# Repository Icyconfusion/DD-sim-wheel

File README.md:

# DD-sim-wheel
A Direct Drive (DD) wheel for simracing using a hoverboard motor and CAN bus.

I designed this wheel for simracing, to compete with high end direct drive wheels that offer great quality force feedback, except with a much lower price. The wheel has the capability to connect wheel rims, pedals, shifters, handbrakes etc and send those inputs, along with steering position to the PC as game inputs. In creating this project, I learned a lot about motor control and half bridge drivers.

# Assembly

The project can be separated into two parts, the wheelbase and the wheel rim.

For the wheelbase, the assembly consists of four horizontal 2020 profiles, allowing for mounting to rigs etc, and providing the basic structure of the base. Two vertical posts are attached by 90 degree connectors to enable mounting the cross beam for the motor.

The crossbeam (2040 profile) is important as it is the base structure for supporting and holding the motor in place. A thin steel plate (necessary to prevent damage and subsequent twisting of the the crossbeam as a result of the motor axle) is attached to the profile, with the flat part of the motor axle being locked on with the 3d printed clamp. This is the mechanism for holding the motor in place and preventing rotation in the axle. 

To prepare the motor, it is first necessary to disassemble it. First remove the tire as this wont be needed. Then remove the motor bell as we will need to drill holes into it. We will also need to drill into the axle. a 6x70mm bolt pattern is drilled in to the bell face, as well as a 30mm hole in the centre. This allows the mounting of the encoder and routing of wires. Drill a hole in the closed end of the axle, so that wires can run through.

The MT6701 encoder is attached to its mount, then press fit into the bearing on the bell side of the motor.

The diametric magnet for the encoder is glued into the hole on the inside of the magnet mount, this will be attached to the motor along with the quick release using the 6x70mm drilled holes.

The side covers attach to the four horizontal profiles using T nuts, and the PSU is mounted to the side cover using the mounting threads in the psu. The PCB is attached to its mount using the mounting holes, then attached to the vertical profile.

The USB C connectors are screwed onto the back plate, and power cables run through the two holes. The back, top and bottom plates/covers are mounted using T nuts.

The front plate is screwed directly into the tapped ends of the profiles. This is the wheelbase assembly.

For the wheel rim assembly, is is as simple as mounting the 12mm buttons using the nuts included, running the cable from the mcu into the USB c connector in the quick release, and then mounting the wheel rim, buttons box/plates and quick release using screws, and then pushing onto wheelbase.

# Electronics

### Schematic

I made my own 3 phase motor driver to handle the control of the hoverboard motor:

It uses an INA240 for current sensing for torque control, and an IR2104 IC so that the STM32 can control the MOSFETS.

Screw terminals to external connections:

And brake resistor circuit:

### PCB

It has M6 mounting holes for the wheelbase PCB mount. The PCB is organised with the motor driver at the top, and low voltage components below the STM32, which is connected by headers. It uses TO-220 mosfets, and 7.62mm screw terminals. The screw terminals on the bottom are to CAN connections, encoder and 5v power.

# Firmware

The wheelbase uses a modified version of OpenFFBoard firmware. OpenFFboard controls the motor including torque, responding to output from the PC/game to provide force feedback. I added my own CAN firmware into this to recieve CAN messages as inputs, and send them to the PC. This included writing my own CAN callback into the firmware.
For the wheel rim MCU, I wrote my own firmware for reading button inputs, and then sending via CAN bus. The MCU will only send a message when their is a change in button states e.g a press or release, this is to reduce interruption to the motor control firmware. The can message is as follows: if button one is pressed, then 00000001, which is 1x01. Or if buttons 1 and 4 are pressed, 00001001, 0x09.

# BOM

### Parts
|    Name                  |                                              Purpose                                                          |  Quantity  | Total cost (USD)      |     Link                                                                                                                                                                                                                                                                                                                                                                                                                                                                                                                                                                                                                                                                                                                                                             | Distributor           |
|------------------------|------------------------------------------------------------------------------------------------------------------------------|----|-------|------------------------------------------------------------------------------------------------------------------------------------------------------------------------------------------------------------------------------------------------------------------------------------------------------------------------------------------------------------------------------------------------------------------------------------------------------------------------------------------------------------------------------------------------------------------------------------------------------------------------------------------------------------------------------------------------------------------------------------------------------------------------------------|------------|
| 10 ohm resistor        | Resistor for the PCB                                                                                                         | 5  | 1.32  | https://www.aliexpress.com/item/1005001437016232.html?spm=a2g0o.productlist.main.25.79ca1H2A1H2AOB&algo_pvid=20ba9475-3400-47e4-a338-b3b9dafa6b8d&algo_exp_id=20ba9475-3400-47e4-a338-b3b9dafa6b8d-22&pdp_ext_f=%7B%22order%22%3A%22131%22%2C%22eval%22%3A%221%22%2C%22fromPage%22%3A%22search%22%7D&pdp_npi=6%40dis%21AUD%211.57%211.41%21%21%211.10%210.99%21%402101dedf17721606578806807eb6a1%2112000016109444174%21sea%21AU%210%21ABX%211%210%21n_tag%3A-29910%3Bd%3A6fbdfe4b%3Bm03_new_user%3A-29895%3BpisId%3A5000000197838623&curPageLogUid=U5uodymgkUGQ&utparam-url=scene%3Asearch%7Cquery_from%3A%7Cx_object_id%3A1005001437016232%7C_p_origin_prod%3A                                                                                                                    | Aliexpress |
| 90 degree brackets     | mounting and assembling T slot profiles                                                                                      | 8  | 0.73  | https://jlcmc.com/product/s/T02/TPDB/die-cast-corner-bracket-eu-20-series-connector?k=TPDB-206-2020&productModelNumber=TPDB-206-2020                                                                                                                                                                                                                                                                                                                                                                                                                                                                                                                                                                                                                                               | JLCMC      |
| T nuts                 | Mounting components to T slot profiles                                                                                       | 60 | 7.23  | https://www.aliexpress.com/item/1005007825040716.html?spm=a2g0o.productlist.main.1.2b5e9Jt29Jt2im&algo_pvid=cbc90c19-296d-4550-b231-f26b2f267562&algo_exp_id=cbc90c19-296d-4550-b231-f26b2f267562-0&pdp_ext_f=%7B%22order%22%3A%223627%22%2C%22spu_best_type%22%3A%22price%22%2C%22eval%22%3A%221%22%2C%22fromPage%22%3A%22search%22%7D&pdp_npi=6%40dis%21AUD%215.45%211.40%21%21%2126.22%216.71%21%402101c59117765644228473233ee706%2112000042345603834%21sea%21AU%216973160092%21ABX%211%210%21n_tag%3A-29910%3Bd%3A6fbdfe4b%3Bm03_new_user%3A-29895%3BpisId%3A5000000203295490&curPageLogUid=qxyuanETgGiG&utparam-url=scene%3Asearch%7Cquery_from%3A%7Cx_object_id%3A1005007825040716%7C_p_origin_prod%3A                                                                       | Aliexpress |
| Screws                 | M5 screws for assembling components. 10 of 16mm, 20 of 14mm, 4 of 30mm, 6 of 45mm, 6 of 65mm, 16 of 8mm. Also 10 of M2x14mm. | 76 | 1.79  | https://jlcmc.com/product/s/E02/EDLA/hex-socket-screw-full-partial-thread-standard-type-(din-912-gb-t-70.1)                                                                                                                                                                                                                                                                                                                                                                                                                                                                                                                                                                                                                                                                        | JLCMC      |
| IR2104                 | IC for powering each phases mosfet                                                                                           | 3  | 2.28  | https://www.aliexpress.com/item/1005005970327760.html?spm=a2g0o.productlist.main.23.5c1bHUXvHUXvA0&algo_pvid=cfa16c6e-e9f8-49b4-b31d-c2c4f5874e03&algo_exp_id=cfa16c6e-e9f8-49b4-b31d-c2c4f5874e03-18&pdp_ext_f=%7B%22order%22%3A%22637%22%2C%22spu_best_type%22%3A%22price%22%2C%22eval%22%3A%221%22%2C%22fromPage%22%3A%22search%22%7D&pdp_npi=6%40dis%21AUD%212.12%212.02%21%21%211.48%211.41%21%402101e81117712033727413624eaf11%2112000035105437556%21sea%21AU%210%21ABX%211%210%21n_tag%3A-29910%3Bd%3A7206fb8d%3Bm03_new_user%3A-29895&curPageLogUid=UiB2F2SOtrNB&utparam-url=scene%3Asearch%7Cquery_from%3A%7Cx_object_id%3A1005005970327760%7C_p_origin_prod%3A                                                                                                           | Aliexpress |
| Small Cap              | 0.47 uF 50V CAP                                                                                                              | 10 | 5.03  | https://www.aliexpress.com/item/1005009938373275.html?spm=a2g0o.productlist.main.5.4b8c770v770vH5&algo_pvid=075c2e82-0ae4-4569-a750-61765aa2f15a&algo_exp_id=075c2e82-0ae4-4569-a750-61765aa2f15a-4&pdp_ext_f=%7B%22order%22%3A%22143%22%2C%22eval%22%3A%221%22%2C%22fromPage%22%3A%22search%22%7D&pdp_npi=6%40dis%21AUD%2111.91%211.41%21%21%2157.24%216.79%21%402101e8f317721561725284158e3d63%2112000050630167302%21sea%21AU%210%21ABX%211%210%21n_tag%3A-29910%3Bd%3A6fbdfe4b%3Bm03_new_user%3A-29895%3BpisId%3A5000000197838560&curPageLogUid=g6TO5H8pSlm0&utparam-url=scene%3Asearch%7Cquery_from%3A%7Cx_object_id%3A1005009938373275%7C_p_origin_prod%3A                                                                                                                    | Aliexpress |
| LM2596                 | Buck converter for supplying low voltage power to the PCB                                                                    | 1  | 2.56  | https://www.aliexpress.com/item/1005010036505161.html?spm=a2g0o.productlist.main.3.245a324a3VAaLL&algo_pvid=f0aaf705-f745-4966-bf3b-609c5fd63b43&algo_exp_id=f0aaf705-f745-4966-bf3b-609c5fd63b43-2&pdp_ext_f=%7B%22order%22%3A%22910%22%2C%22eval%22%3A%221%22%2C%22fromPage%22%3A%22search%22%7D&pdp_npi=6%40dis%21AUD%213.57%212.47%21%21%2117.17%2111.85%21%402101c59117764972466628438ee704%2112000050905433462%21sea%21AU%216973160092%21ABX%211%210%21n_tag%3A-29910%3Bd%3A6fbdfe4b%3Bm03_new_user%3A-29895&curPageLogUid=02yFEsARBKx0&utparam-url=scene%3Asearch%7Cquery_from%3A%7Cx_object_id%3A1005010036505161%7C_p_origin_prod%3A                                                                                                                                      | Aliexpress |
| INA240                 | The current amplifier to sense motor current with the shunt                                                                  | 3  | 11.48 | https://www.aliexpress.com/item/1005007050377087.html?spm=a2g0o.productlist.main.1.59bb640dmD6bm9&algo_pvid=5660d2fb-76d0-4ac9-8936-9aaff13eced9&algo_exp_id=5660d2fb-76d0-4ac9-8936-9aaff13eced9-0&pdp_ext_f=%7B%22order%22%3A%2288%22%2C%22spu_best_type%22%3A%22price%22%2C%22eval%22%3A%221%22%2C%22fromPage%22%3A%22search%22%7D&pdp_npi=6%40dis%21AUD%215.29%215.29%21%21%213.68%213.68%21%402101e2b417719031354937568ebc74%2112000039231521353%21sea%21AU%210%21ABX%211%210%21n_tag%3A-29910%3Bd%3A7206fb8d%3Bm03_new_user%3A-29895&curPageLogUid=PooybKR7LpTQ&utparam-url=scene%3Asearch%7Cquery_from%3A%7Cx_object_id%3A1005007050377087%7C_p_origin_prod%3A#nav-specification                                                                                            | Aliexpress |
| MOSFET                 | IRF2204 mosfet for the 3 phase motor driver                                                                                  | 3  | 5.63  | https://www.aliexpress.com/item/1005008398718849.html?spm=a2g0o.productlist.main.5.253d37aaB6oOcP&algo_pvid=968fc11d-b1d2-4afe-80e2-908033e5c1a2&algo_exp_id=968fc11d-b1d2-4afe-80e2-908033e5c1a2-4&pdp_ext_f=%7B%22order%22%3A%2215%22%2C%22eval%22%3A%221%22%2C%22fromPage%22%3A%22search%22%7D&pdp_npi=6%40dis%21AUD%216.13%216.13%21%21%2129.42%2129.42%21%402101e62517719020271583311e1467%2112000045693925609%21sea%21AU%210%21ABX%211%210%21n_tag%3A-29910%3Bd%3A7206fb8d%3Bm03_new_user%3A-29895&curPageLogUid=EANWfiNw3IgJ&utparam-url=scene%3Asearch%7Cquery_from%3A%7Cx_object_id%3A1005008398718849%7C_p_origin_prod%3A                                                                                                                                                | Aliexpress |
| Large Cap              | 50V 2200uF capacitor for smoothing across power lines                                                                        | 1  | 12.76 | https://www.aliexpress.com/item/1005005380342459.html?spm=a2g0o.productlist.main.1.1cb3wyyqwyyqgA&algo_pvid=0e70eac5-46e9-46e6-a3a2-8b9773f8851b&algo_exp_id=0e70eac5-46e9-46e6-a3a2-8b9773f8851b-0&pdp_ext_f=%7B%22order%22%3A%22161%22%2C%22eval%22%3A%221%22%2C%22fromPage%22%3A%22search%22%7D&pdp_npi=6%40dis%21AUD%2114.12%217.00%21%21%219.92%214.92%21%402101e81117721554588813670e5db8%2112000032819089773%21sea%21AU%210%21ABX%211%210%21n_tag%3A-29910%3Bd%3A6fbdfe4b%3Bm03_new_user%3A-29895%3BpisId%3A5000000197838525&curPageLogUid=RPVryHdchNX4&utparam-url=scene%3Asearch%7Cquery_from%3A%7Cx_object_id%3A1005005380342459%7C_p_origin_prod%3A                                                                                                                     | Aliexpress |
| MT6701                 | The MT6701 is the encoder to track the position of the wheel rim.                                                            | 1  | 3.27  | https://www.aliexpress.com/item/1005010143099990.html?spm=a2g0o.productlist.main.6.f71b6d7eaJZaGf&algo_pvid=75d2c31f-2426-4c4f-a325-0492f0b931a5&algo_exp_id=75d2c31f-2426-4c4f-a325-0492f0b931a5-5&pdp_ext_f=%7B%22order%22%3A%22143%22%2C%22eval%22%3A%221%22%2C%22fromPage%22%3A%22search%22%7D&pdp_npi=6%40dis%21AUD%214.35%211.42%21%21%213.04%210.99%21%402101f11417712044155591620ecc83%2112000051300485458%21sea%21AU%210%21ABX%211%210%21n_tag%3A-29910%3Bd%3A7206fb8d%3Bm03_new_user%3A-29895%3BpisId%3A5000000197843456&curPageLogUid=xzfgW3svUKzg&utparam-url=scene%3Asearch%7Cquery_from%3A%7Cx_object_id%3A1005010143099990%7C_p_origin_prod%3A                                                                                                                      | Aliexpress |
| STM32                  | STM32 is the wheelbase PCB MCU. It runs the FFB firmware.                                                                    | 1  | 10.62 | https://www.aliexpress.com/item/1005009620785965.html?spm=a2g0o.productlist.main.1.535d15630eiPky&algo_pvid=2c8f865b-70be-4e0e-94db-818f2531dcac&algo_exp_id=2c8f865b-70be-4e0e-94db-818f2531dcac-0&pdp_ext_f=%7B%22order%22%3A%22555%22%2C%22spu_best_type%22%3A%22price%22%2C%22eval%22%3A%221%22%2C%22fromPage%22%3A%22search%22%7D&pdp_npi=6%40dis%21AUD%2113.99%2113.99%21%21%2167.23%2167.23%21%402101e2b217721562525755548e8f87%2112000049659011407%21sea%21AU%210%21ABX%211%210%21n_tag%3A-29910%3Bd%3A6fbdfe4b%3Bm03_new_user%3A-29895&curPageLogUid=iACQ9ztcidY0&utparam-url=scene%3Asearch%7Cquery_from%3A%7Cx_object_id%3A1005009620785965%7C_p_origin_prod%3A#nav-description                                                                                         | Aliexpress |
| TVS diode              | P6KE36A TVS diode for power on the PCB                                                                                       | 1  | 2.66  | https://www.aliexpress.com/item/1005008668996384.html?spm=a2g0o.productlist.main.3.4aafzSRuzSRuEZ&algo_pvid=bd2191ac-a9e6-4fb8-a882-36100d407a63&algo_exp_id=bd2191ac-a9e6-4fb8-a882-36100d407a63-2&pdp_ext_f=%7B%22order%22%3A%2243%22%2C%22eval%22%3A%221%22%2C%22fromPage%22%3A%22search%22%7D&pdp_npi=6%40dis%21AUD%213.71%213.71%21%21%2117.85%2117.85%21%402101d49617721566134604795e8004%2112000046167790507%21sea%21AU%210%21ABX%211%210%21n_tag%3A-29910%3Bd%3A6fbdfe4b%3Bm03_new_user%3A-29895&curPageLogUid=yzE7XJPgJBo8&utparam-url=scene%3Asearch%7Cquery_from%3A%7Cx_object_id%3A1005008668996384%7C_p_origin_prod%3A                                                                                                                                                | Aliexpress |
| RP2350                 | RP2350 CAN is the devboard for the wheel rim. It has CAN included.                                                           | 1  | 16.93 | https://www.aliexpress.com/item/1005008827015596.html?spm=a2g0o.productlist.main.27.7dfe5801TplWA9&algo_pvid=08775c8d-70db-4dc4-a46c-ab64ce72b444&algo_exp_id=08775c8d-70db-4dc4-a46c-ab64ce72b444-26&pdp_ext_f=%7B%22order%22%3A%2230%22%2C%22spu_best_type%22%3A%22price%22%2C%22eval%22%3A%221%22%2C%22fromPage%22%3A%22search%22%7D&pdp_npi=6%40dis%21AUD%2123.39%2123.39%21%21%2116.43%2116.43%21%402103129f17721471691216473e4379%2112000046843840523%21sea%21AU%210%21ABX%211%210%21n_tag%3A-29910%3Bd%3A6fbdfe4b%3Bm03_new_user%3A-29895&curPageLogUid=vOb7IYHAYoA1&utparam-url=scene%3Asearch%7Cquery_from%3A%7Cx_object_id%3A1005008827015596%7C_p_origin_prod%3A                                                                                                        | Aliexpress |
| CAN resistor           | 120 ohm termination resistor for CAN bus.                                                                                    | 2  | 1.35  | https://www.aliexpress.com/item/1005006730653425.html?spm=a2g0o.productlist.main.3.71e2DHFsDHFsBo&algo_pvid=4792a58b-ba7d-417a-a8f9-6b9100778656&algo_exp_id=4792a58b-ba7d-417a-a8f9-6b9100778656-2&pdp_ext_f=%7B%22order%22%3A%22186%22%2C%22eval%22%3A%221%22%2C%22fromPage%22%3A%22search%22%7D&pdp_npi=6%40dis%21AUD%211.81%211.41%21%21%211.27%210.99%21%402103212517721604286903793e9d23%2112000038116126737%21sea%21AU%210%21ABX%211%210%21n_tag%3A-29910%3Bd%3A6fbdfe4b%3Bm03_new_user%3A-29895%3BpisId%3A5000000197838588&curPageLogUid=c0lLXeUYCSua&utparam-url=scene%3Asearch%7Cquery_from%3A%7Cx_object_id%3A1005006730653425%7C_p_origin_prod%3A                                                                                                                      | Aliexpress |
| Shunt resistor         | Constantan wire resistor for motor current sensing. 10mr 1.5x20                                                              | 3  | 1.63  | https://www.aliexpress.com/item/1005003122854809.html?spm=a2g0o.productlist.main.3.74b0DwvBDwvB9C&aem_p4p_detail=202602231921512450754371729030011352552&algo_pvid=0917fda2-6079-4745-8ca0-69a6caeb421b&algo_exp_id=0917fda2-6079-4745-8ca0-69a6caeb421b-3&pdp_ext_f=%7B%22order%22%3A%22430%22%2C%22eval%22%3A%221%22%2C%22fromPage%22%3A%22search%22%7D&pdp_npi=6%40dis%21AUD%212.26%211.42%21%21%211.57%210.99%21%40210311c217719033114376370e5c18%2112000024218873110%21sea%21AU%210%21ABX%211%210%21n_tag%3A-29910%3Bd%3A7206fb8d%3Bm03_new_user%3A-29895%3BpisId%3A5000000197843401&curPageLogUid=jjHaL1Mq2xuj&utparam-url=scene%3Asearch%7Cquery_from%3A%7Cx_object_id%3A1005003122854809%7C_p_origin_prod%3A&search_p4p_id=202602231921512450754371729030011352552_1       | Aliexpress |
| Push Buttons           | The pushbuttons are used for the steering rim as the controls.                                                               | 8  | 1.54  | https://www.aliexpress.com/item/1005006341090307.html?spm=a2g0o.productlist.main.20.5cf57361Y8YztK&aem_p4p_detail=20260226150251321058939507660012928276&algo_pvid=4d10b748-2f81-4e0f-bd65-9ed277464cad&algo_exp_id=4d10b748-2f81-4e0f-bd65-9ed277464cad-19&pdp_ext_f=%7B%22order%22%3A%2217%22%2C%22eval%22%3A%221%22%2C%22fromPage%22%3A%22search%22%7D&pdp_npi=6%40dis%21AUD%212.14%212.14%21%21%2110.29%2110.29%21%40210328df17721469715053191e2c7c%2112000036820867468%21sea%21AU%210%21ABX%211%210%21n_tag%3A-29910%3Bd%3A6fbdfe4b%3Bm03_new_user%3A-29895&curPageLogUid=qpi8KIvDRT09&utparam-url=scene%3Asearch%7Cquery_from%3A%7Cx_object_id%3A1005006341090307%7C_p_origin_prod%3A&search_p4p_id=20260226150251321058939507660012928276_6                                 | Aliexpress |
| CAN transciever        | SN65HVD230 Can transceiver for communicating between wheelbase and wheel rim                                                 | 1  | 3.93  | https://www.aliexpress.com/item/1005006693506982.html?spm=a2g0o.productlist.main.5.2e092eb7tfUtti&algo_pvid=6bbce969-288b-40fc-94ae-1be761e42c9e&algo_exp_id=6bbce969-288b-40fc-94ae-1be761e42c9e-4&pdp_ext_f=%7B%22order%22%3A%22173%22%2C%22eval%22%3A%221%22%2C%22fromPage%22%3A%22search%22%7D&pdp_npi=6%40dis%21AUD%215.45%215.45%21%21%2126.12%2126.12%21%402101e2b217719045860566401e30ac%2112000050142930102%21sea%21AU%210%21ABX%211%210%21n_tag%3A-29910%3Bd%3A7206fb8d%3Bm03_new_user%3A-29895&curPageLogUid=lR7HKQJall19&utparam-url=scene%3Asearch%7Cquery_from%3A%7Cx_object_id%3A1005006693506982%7C_p_origin_prod%3A                                                                                                                                               | Aliexpress |
| Brake resistor         | 500W 3.3R brake resistor for motor control                                                                                   | 1  | 20.19 | https://www.aliexpress.com/item/1005002672337729.html?spm=a2g0o.productlist.main.48.195cyrM4yrM4qr&algo_pvid=01faf767-fab9-4b6c-bf52-cc127d8ba5a5&algo_exp_id=01faf767-fab9-4b6c-bf52-cc127d8ba5a5-47&pdp_ext_f=%7B%22order%22%3A%221643%22%2C%22eval%22%3A%221%22%2C%22fromPage%22%3A%22search%22%7D&pdp_npi=6%40dis%21AUD%2111.50%211.41%21%21%218.08%210.99%21%402101e62517721567573211903ef9cf%2112000021648744011%21sea%21AU%210%21ABX%211%210%21n_tag%3A-29910%3Bd%3A6fbdfe4b%3Bm03_new_user%3A-29895%3BpisId%3A5000000197838595&curPageLogUid=hIX4clt2NvSe&utparam-url=scene%3Asearch%7Cquery_from%3A%7Cx_object_id%3A1005002672337729%7C_p_origin_prod%3A#nav-specification                                                                                                | Aliexpress |
| Steering wheel         | The steering wheel rim                                                                                                       | 1  | 23.10 | https://www.aliexpress.com/item/1005008283871869.html?spm=a2g0o.productlist.main.5.430722Bl22BlMr&algo_pvid=c2dc1e47-fc69-493c-8cef-484f19cfbc0e&algo_exp_id=c2dc1e47-fc69-493c-8cef-484f19cfbc0e-4&pdp_ext_f=%7B%22order%22%3A%227%22%2C%22eval%22%3A%221%22%2C%22fromPage%22%3A%22search%22%7D&pdp_npi=6%40dis%21AUD%2135.77%2132.19%21%21%21171.89%21154.69%21%40210319b717721466880308911e4c93%2112000044476687786%21sea%21AU%210%21ABX%211%210%21n_tag%3A-29910%3Bd%3A6fbdfe4b%3Bm03_new_user%3A-29895&curPageLogUid=euxCJDX6zvuV&utparam-url=scene%3Asearch%7Cquery_from%3A%7Cx_object_id%3A1005008283871869%7C_p_origin_prod%3A                                                                                                                                             | Aliexpress |
| Quick release          | Quick release for mechanically attaching the rim to the wheelbase                                                            | 1  | 30.44 | https://www.aliexpress.com/item/1005006011448738.html?spm=a2g0o.productlist.main.31.64316a3e9iB9GD&algo_pvid=a887161b-c5d8-4da6-b413-c2813b075eea&algo_exp_id=a887161b-c5d8-4da6-b413-c2813b075eea-28&pdp_ext_f=%7B%22order%22%3A%221330%22%2C%22spu_best_type%22%3A%22price%22%2C%22eval%22%3A%221%22%2C%22fromPage%22%3A%22search%22%7D&pdp_npi=6%40dis%21AUD%2137.14%2129.81%21%21%21178.48%21143.25%21%4021033d9d17721600855956035edb11%2112000044198059347%21sea%21AU%210%21ABX%211%210%21n_tag%3A-29910%3Bd%3A6fbdfe4b%3Bm03_new_user%3A-29895%3BpisId%3A5000000197838525&curPageLogUid=kRrVs4aPaLjf&utparam-url=scene%3Asearch%7Cquery_from%3A%7Cx_object_id%3A1005006011448738%7C_p_origin_prod%3A                                                                         | Aliexpress |
| USB C male connector   | For use in the steering rim to connect it and transfer data/power to and from the wheelbase                                  | 1  | 3.51  | https://www.aliexpress.com/item/1005009243305185.html?spm=a2g0o.productlist.main.5.69a21c5fyiIEjy&algo_pvid=44eab888-692e-4da2-b96a-8381b9425e2a&algo_exp_id=44eab888-692e-4da2-b96a-8381b9425e2a-4&pdp_ext_f=%7B%22order%22%3A%22284%22%2C%22eval%22%3A%221%22%2C%22fromPage%22%3A%22search%22%7D&pdp_npi=6%40dis%21AUD%214.62%211.42%21%21%2122.13%216.82%21%402101e81117719025451461074eaf10%2112000048447657808%21sea%21AU%210%21ABX%211%210%21n_tag%3A-29910%3Bd%3A7206fb8d%3Bm03_new_user%3A-29895%3BpisId%3A5000000197843456&curPageLogUid=0OJ39zZ4TCBB&utparam-url=scene%3Asearch%7Cquery_from%3A%7Cx_object_id%3A1005009243305185%7C_p_origin_prod%3A#nav-description                                                                                                     | Aliexpress |
| USB C female connector | For connecting pedals, handbrake etc to the wheelbase. They are also used for connecting the rim.                            | 5  | 2.04  | https://www.aliexpress.com/item/1005008529430881.html?spm=a2g0o.productlist.main.25.31565a56h2lBC9&algo_pvid=3489dd88-14fb-466a-ad81-588128104914&algo_exp_id=3489dd88-14fb-466a-ad81-588128104914-22&pdp_ext_f=%7B%22order%22%3A%22918%22%2C%22eval%22%3A%221%22%2C%22fromPage%22%3A%22search%22%7D&pdp_npi=6%40dis%21AUD%212.14%211.42%21%21%2110.27%216.82%21%402101e80317719023676641149eaa59%2112000045578295667%21sea%21AU%210%21ABX%211%210%21n_tag%3A-29910%3Bd%3A7206fb8d%3Bm03_new_user%3A-29895%3BpisId%3A5000000198344600&curPageLogUid=Uu7WJVr0K4pu&utparam-url=scene%3Asearch%7Cquery_from%3A%7Cx_object_id%3A1005008529430881%7C_p_origin_prod%3A#nav-description                                                                                                   | Aliexpress |
| PSU                    | 36v 800w psu for driving the motor and electronics                                                                           | 1  | 27.31 | https://www.aliexpress.com/item/1005010376385581.html?spm=a2g0o.productlist.main.1.7bb1IOe3IOe3jY&algo_pvid=2147334e-4a18-4dc9-b4e5-168b44d118d0&algo_exp_id=2147334e-4a18-4dc9-b4e5-168b44d118d0-0&pdp_ext_f=%7B%22order%22%3A%222227%22%2C%22eval%22%3A%221%22%2C%22orig_sl_item_id%22%3A%221005010376385581%22%2C%22orig_item_id%22%3A%221005010130797577%22%2C%22fromPage%22%3A%22search%22%7D&pdp_npi=6%40dis%21AUD%2158.78%2111.60%21%21%21282.44%2155.73%21%402101f70717721605308621698e5ab6%2112000053303189861%21sea%21AU%210%21ABX%211%210%21n_tag%3A-29910%3Bd%3A6fbdfe4b%3Bm03_new_user%3A-29895%3BpisId%3A5000000198344600&curPageLogUid=77qK0odrpWPv&utparam-url=scene%3Asearch%7Cquery_from%3A%7Cx_object_id%3A1005010376385581%7C_p_origin_prod%3A1005010130797577 | Alixpress  |
| Hoverboard motor       | 36v 350w hoverboard motor to provide the force feedback.                                                                     | 1  | 32.22 | https://www.aliexpress.com/item/1005009897349541.html?spm=a2g0o.productlist.main.1.1a428KJE8KJEon&algo_pvid=ad5b7875-e0f4-4d88-8ac9-d6291cc793fe&algo_exp_id=ad5b7875-e0f4-4d88-8ac9-d6291cc793fe-0&pdp_ext_f=%7B%22order%22%3A%2230%22%2C%22spu_best_type%22%3A%22price%22%2C%22eval%22%3A%221%22%2C%22fromPage%22%3A%22search%22%7D&pdp_npi=6%40dis%21AUD%21110.16%2134.89%21%21%21527.59%21167.08%21%402101c44517719023114054527ef8c1%2112000050511139857%21sea%21AU%210%21ABX%211%210%21n_tag%3A-29910%3Bd%3A7206fb8d%3Bm03_new_user%3A-29895%3BpisId%3A5000000197843401&curPageLogUid=29wSyuul6Ael&utparam-url=scene%3Asearch%7Cquery_from%3A%7Cx_object_id%3A1005009897349541%7C_p_origin_prod%3A                                                                            | Aliexpress |
| Steel plate            | For clamping the motor shaft and protecting the aluminium crossbeam. 3mm thick.                                              | 1  | 9.29  | https://www.aliexpress.com/item/1005007253220639.html?spm=a2g0o.productlist.main.7.105374b0Vo9Lnp&algo_pvid=d2ee90d7-dfa6-4ef8-ba77-ae4972b544d1&algo_exp_id=d2ee90d7-dfa6-4ef8-ba77-ae4972b544d1-6&pdp_ext_f=%7B%22order%22%3A%22693%22%2C%22eval%22%3A%221%22%2C%22fromPage%22%3A%22search%22%7D&pdp_npi=6%40dis%21AUD%213.74%211.40%21%21%212.64%210.99%21%40210311c217764913486386872ee44c%2112000039956645420%21sea%21AU%216973160092%21ABX%211%210%21n_tag%3A-29910%3Bd%3A6fbdfe4b%3Bm03_new_user%3A-29895%3BpisId%3A5000000203295561&curPageLogUid=3KQb5Kkc63sV&utparam-url=scene%3Asearch%7Cquery_from%3A%7Cx_object_id%3A1005007253220639%7C_p_origin_prod%3A                                                                                                             | Aliexpress |
| 2040 T slot 180mm      | The crossbeam for supporting the motor shaft.                                                                                | 1  | 0.80  | https://jlcmc.com/product/s/T01/TXCJ/extruded-aluminum-t-slot-20-series(eu)                                                                                                                                                                                                                                                                                                                                                                                                                                                                                                                                                                                                                                                                                                        | JLCMC      |
| T slot 200mm           | The vertical supports for 2060, PCB and PSU                                                                                  | 2  | 1.05  | https://jlcmc.com/product/s/T01/TXCJ/extruded-aluminum-t-slot-20-series(eu)                                                                                                                                                                                                                                                                                                                                                                                                                                                                                                                                                                                                                                                                                                        | JLCMC      |
| T slot 320mm           | Providing the outer horizontal frame                                                                                         | 4  | 3.28  | https://jlcmc.com/product/s/T01/TXCJ/extruded-aluminum-t-slot-20-series(eu)                                                                                                                                                                                                                                                                                                                                                                                                                                                                                                                                                                                                                                                                                                        | JLCMC |

### Printed parts

| Name| Quantity|Picture|
|---|---|---|
|Side cover| 1|
|PSU side cover| 1|
|Top plate | 1|
|Top cover| 1|
|Bottom cover| 1|
|Back cover| 1|
|Front cover| 1|
|Axle clamp| 1|
|Encoder module| 1|
|Magnet module| 1|
|PCB mount| 1|
|Wheel button plate| 1|

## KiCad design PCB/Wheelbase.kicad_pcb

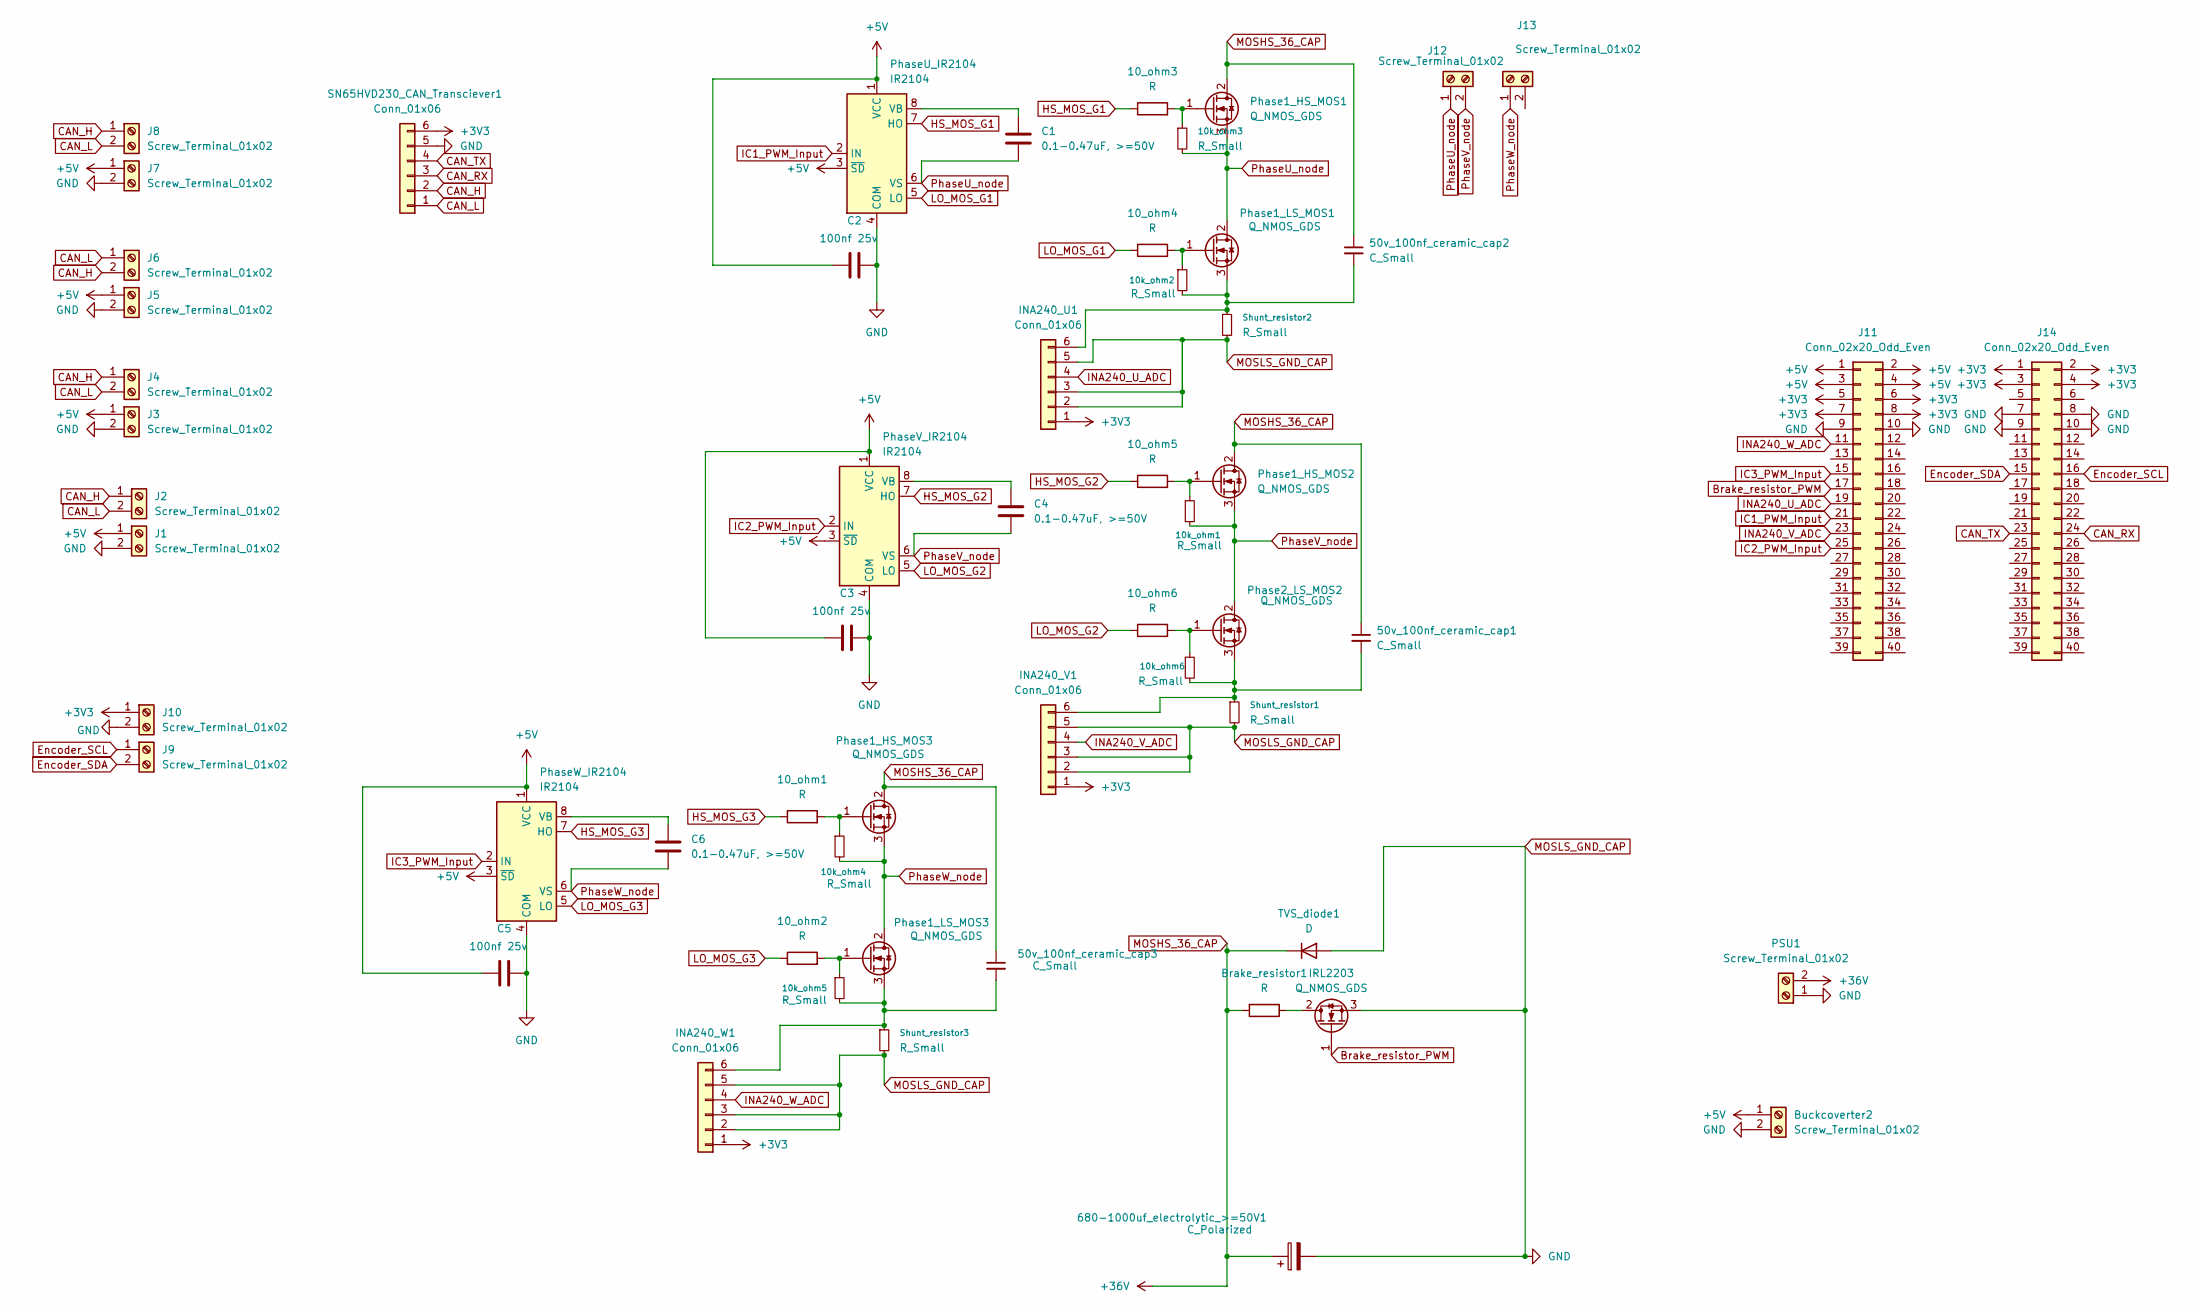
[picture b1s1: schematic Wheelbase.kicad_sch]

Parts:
10_ohm1, 10_ohm2, 10_ohm3, 10_ohm4, 10_ohm5, 10_ohm6: R; R_Axial_DIN0207_L6.3mm_D2.5mm_P5.08mm_Vertical
10k_ohm1, 10k_ohm2, 10k_ohm3, 10k_ohm4, 10k_ohm5, 10k_ohm6: R_Small; R_Axial_DIN0207_L6.3mm_D2.5mm_P5.08mm_Vertical
50v_100nf_ceramic_cap1, 50v_100nf_ceramic_cap2, 50v_100nf_ceramic_cap3: C_Small; C_Disc_D7.5mm_W5.0mm_P7.50mm
680-1000uf_electrolytic_>=50V1: C_Polarized; CP_Radial_D12.5mm_P2.50mm
Brake_resistor1: R; Wuerth_691311400102_P7.62mm
Buckcoverter2: Screw_Terminal_01x02; Wuerth_691311400102_P7.62mm
C1, C4, C6: 0.1-0.47uF, >=50V; CP_Radial_D5.0mm_P2.50mm
C2, C3, C5: 100nf 25v; C_Disc_D5.0mm_W2.5mm_P2.50mm
INA240_U1, INA240_V1, INA240_W1: Conn_01x06; PinHeader_1x06_P2.54mm_Vertical
IRL2203: Q_NMOS_GDS; TO-220-3_Vertical
J1, J2, J3, J4, J5, J6, J7, J8, J9, J10, J12, J13: Screw_Terminal_01x02; Wuerth_691311400102_P7.62mm
J11, J14: Conn_02x20_Odd_Even; PinHeader_2x20_P2.54mm_Vertical
PSU1: Screw_Terminal_01x02; Wuerth_691311400102_P7.62mm
Phase1_HS_MOS1, Phase1_HS_MOS2, Phase1_HS_MOS3, Phase1_LS_MOS1, Phase1_LS_MOS3, Phase2_LS_MOS2: Q_NMOS_GDS; TO-220-3_Vertical
PhaseU_IR2104: IR2104; DIP-8_W7.62mm
PhaseV_IR2104: IR2104; DIP-8_W7.62mm
PhaseW_IR2104: IR2104; DIP-8_W7.62mm
SN65HVD230_CAN_Transciever1: Conn_01x06; PinHeader_1x06_P2.54mm_Vertical
Shunt_resistor1, Shunt_resistor2, Shunt_resistor3: R_Small; R_Axial_Power_L20.0mm_W6.4mm_P22.40mm
TVS_diode1: D; D_T-1_P5.08mm_Horizontal

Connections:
+3V3: INA240_U1.1, INA240_V1.1, INA240_W1.1, J10.1, J11.5, J11.6, J11.7, J11.8, J14.1, J14.2, J14.3, J14.4, SN65HVD230_CAN_Transciever1.6
+5V: Buckcoverter2.1, C2.1, C3.1, C5.1, J1.1, J3.1, J5.1, J7.1, J11.1, J11.2, J11.3, J11.4, PhaseU_IR2104.1 (VCC), PhaseU_IR2104.3 (~SD), PhaseV_IR2104.1 (VCC), PhaseV_IR2104.3 (~SD), PhaseW_IR2104.1 (VCC), PhaseW_IR2104.3 (~SD)
Brake_resistor_PWM: IRL2203.1 (G), J11.17
CAN_H: J2.1, J4.1, J6.2, J8.1, SN65HVD230_CAN_Transciever1.2
CAN_L: J2.2, J4.2, J6.1, J8.2, SN65HVD230_CAN_Transciever1.1
CAN_RX: J14.24, SN65HVD230_CAN_Transciever1.3
CAN_TX: J14.23, SN65HVD230_CAN_Transciever1.4
Encoder_SCL: J9.1, J14.16
Encoder_SDA: J9.2, J14.15
HS_MOS_G1: 10_ohm3.1, PhaseU_IR2104.7 (HO)
HS_MOS_G2: 10_ohm5.1, PhaseV_IR2104.7 (HO)
HS_MOS_G3: 10_ohm1.1, PhaseW_IR2104.7 (HO)
IC1_PWM_Input: J11.21, PhaseU_IR2104.2 (IN)
IC2_PWM_Input: J11.25, PhaseV_IR2104.2 (IN)
IC3_PWM_Input: J11.15, PhaseW_IR2104.2 (IN)
INA240_U_ADC: INA240_U1.4, J11.19
INA240_V_ADC: INA240_V1.4, J11.23
INA240_W_ADC: INA240_W1.4, J11.11
LO_MOS_G1: 10_ohm4.1, PhaseU_IR2104.5 (LO)
LO_MOS_G2: 10_ohm6.1, PhaseV_IR2104.5 (LO)
LO_MOS_G3: 10_ohm2.1, PhaseW_IR2104.5 (LO)
MOSHS_36_CAP: 50v_100nf_ceramic_cap1.1, 50v_100nf_ceramic_cap2.1, 50v_100nf_ceramic_cap3.1, 680-1000uf_electrolytic_>=50V1.1, Brake_resistor1.2, PSU1.2, Phase1_HS_MOS1.2 (D), Phase1_HS_MOS2.2 (D), Phase1_HS_MOS3.2 (D), TVS_diode1.1 (K); also elsewhere on the board
MOSLS_GND_CAP: 680-1000uf_electrolytic_>=50V1.2, Buckcoverter2.2, C2.2, C3.2, C5.2, INA240_U1.2, INA240_U1.3, INA240_U1.5, INA240_V1.2, INA240_V1.3, INA240_V1.5, INA240_W1.2, INA240_W1.3, INA240_W1.5, IRL2203.3 (S), J1.2, J3.2, J5.2, J7.2, J10.2, J11.9, J11.10, J14.7, J14.8, J14.9, J14.10, PSU1.1, PhaseU_IR2104.4 (COM), PhaseV_IR2104.4 (COM), PhaseW_IR2104.4 (COM), SN65HVD230_CAN_Transciever1.5, Shunt_resistor1.2, Shunt_resistor2.2, Shunt_resistor3.2, TVS_diode1.2 (A)
unnamed 23: 10k_ohm2.2, 50v_100nf_ceramic_cap2.2, INA240_U1.6, Phase1_LS_MOS1.3 (S), Shunt_resistor2.1; also elsewhere on the board
unnamed 24: 10k_ohm6.2, 50v_100nf_ceramic_cap1.2, INA240_V1.6, Phase2_LS_MOS2.3 (S), Shunt_resistor1.1; also elsewhere on the board
unnamed 25: 10k_ohm5.2, 50v_100nf_ceramic_cap3.2, INA240_W1.6, Phase1_LS_MOS3.3 (S), Shunt_resistor3.1; also elsewhere on the board
unnamed: Brake_resistor1.1, IRL2203.2 (D)
unnamed: 10_ohm3.2, 10k_ohm3.1, Phase1_HS_MOS1.1 (G)
unnamed: 10_ohm5.2, 10k_ohm1.1, Phase1_HS_MOS2.1 (G)
unnamed: 10_ohm1.2, 10k_ohm4.1, Phase1_HS_MOS3.1 (G)
unnamed: 10_ohm4.2, 10k_ohm2.1, Phase1_LS_MOS1.1 (G)
unnamed: 10_ohm2.2, 10k_ohm5.1, Phase1_LS_MOS3.1 (G)
unnamed: 10_ohm6.2, 10k_ohm6.1, Phase2_LS_MOS2.1 (G)
unnamed: C1.1, PhaseU_IR2104.8 (VB)
unnamed: C4.1, PhaseV_IR2104.8 (VB)
unnamed: C6.1, PhaseW_IR2104.8 (VB)
PhaseU_node: 10k_ohm3.2, C1.2, J12.1, Phase1_HS_MOS1.3 (S), Phase1_LS_MOS1.2 (D), PhaseU_IR2104.6 (VS)
PhaseV_node: 10k_ohm1.2, C4.2, J12.2, Phase1_HS_MOS2.3 (S), Phase2_LS_MOS2.2 (D), PhaseV_IR2104.6 (VS)
PhaseW_node: 10k_ohm4.2, C6.2, J13.1, Phase1_HS_MOS3.3 (S), Phase1_LS_MOS3.2 (D), PhaseW_IR2104.6 (VS)

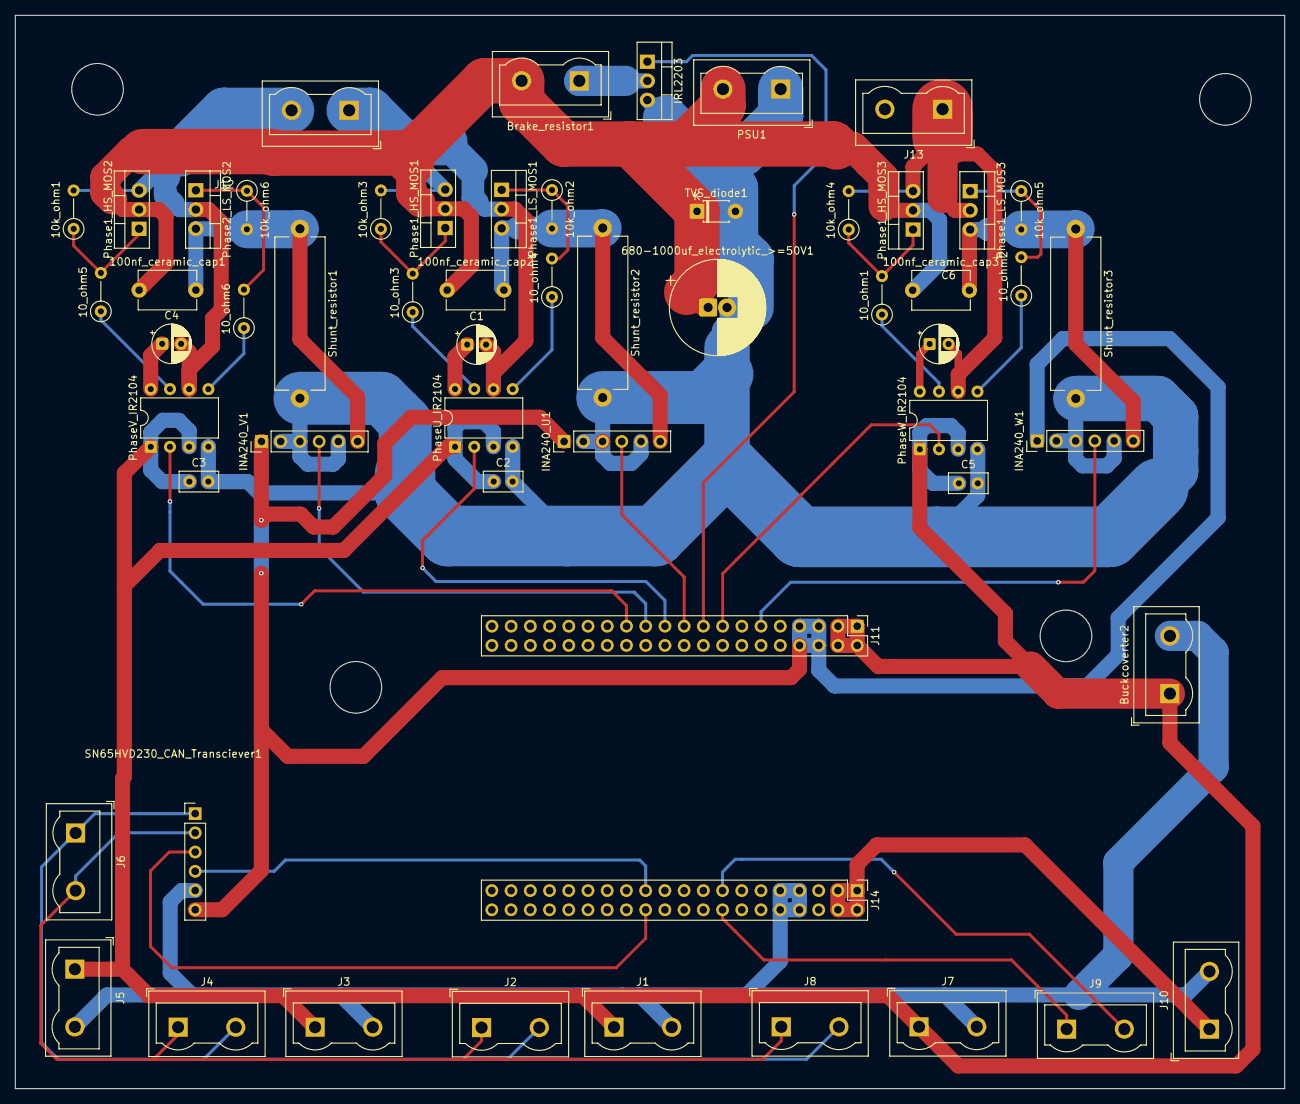
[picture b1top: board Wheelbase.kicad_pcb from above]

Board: 2 copper layers, 167.7 x 141.8 mm, 57 parts (0 on the bottom side), 39 nets.

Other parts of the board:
100nf_ceramic_cap1, 100nf_ceramic_cap2, 100nf_ceramic_cap3: C_Small; C_Disc_D7.5mm_W5.0mm_P7.50mm

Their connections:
MOSHS_36_CAP: 100nf_ceramic_cap1.1, 100nf_ceramic_cap2.1, 100nf_ceramic_cap3.1; also elsewhere on the board
unnamed 23: 100nf_ceramic_cap2.2; also elsewhere on the board
unnamed 24: 100nf_ceramic_cap1.2; also elsewhere on the board
unnamed 25: 100nf_ceramic_cap3.2; also elsewhere on the board

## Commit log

2026-04-19 Rename Encoder module.step to CAD/Encoder module.step
2026-04-19 Rename Front cover.step to CAD/Front cover.step
2026-04-19 Rename Magnet module.step to CAD/Magnet module.step
2026-04-19 Rename PCB mount.step to CAD/PCB mount.step
2026-04-19 Rename Top cover.step to CAD/Top cover.step
2026-04-19 Rename Top plate.step to CAD/Top plate.step
2026-04-19 Rename Wheel button plate.step to CAD/Wheel button plate.step
2026-04-19 Rename bottom plate.step to CAD/bottom plate.step
2026-04-19 Rename side cover psu side.step to CAD/side cover psu side.step
2026-04-19 Rename side cover.step to CAD/side cover.step
2026-04-19 Rename Back plate.step to CAD/Back plate.step
2026-04-19 Rename Wheelbase.kicad_pcb to PCB/Wheelbase.kicad_pcb
2026-04-19 Rename Wheelbase.kicad_prl to PCB/Wheelbase.kicad_prl
2026-04-19 Rename Wheelbase.kicad_pro to PCB/Wheelbase.kicad_pro
2026-04-19 Rename Wheelbase.kicad_sch to PCB/Wheelbase.kicad_sch
2026-04-19 Rename platformio.ini to Firmware/platformio.ini
2026-04-19 Rename OpenFFBoard-master.zip to Firmware/OpenFFBoard-master.zip
2026-04-19 Rename Makefile to Firmware/Makefile
2026-04-19 Rename .project to Firmware/.project
